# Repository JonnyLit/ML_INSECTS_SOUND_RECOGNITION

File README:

Contenuto di questa cartella:

.
├── ESP32_Code							Codice per Arduino-IDE da usare sulle ESP32.
├── 4-classes_Training_ML_Code			Codice per effettuare il training della rete neurale basata su dataset "SBCM (Smart Bee Colony Monitor)" a 4 classi.
├── RaspberryPi_Code					Replica dei path del RaspberryPi dove sono contenuti il codice del Server (python) che deve comunicare con gli esp32 ed effettuare l'inference degli audio.
├── Sensors_Network_Simulator_Code		Codici Python che simulano in modo 1:1 i codici per esp32 e per RaspberryPi (quest'ultimo è uguale a quello del Server che gira su RaspberryPi).
└── Kicad9_projects_folder				Progetto Low quiescent current board with ESP32

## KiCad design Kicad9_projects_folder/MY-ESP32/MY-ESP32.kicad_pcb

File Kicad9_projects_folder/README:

The Kicad9 project is named "MY-ESP32".

The project consists in an ESP32 board for LiFePO4 3.6V batteries or USB use,
where the quiescent currents are low in order to use the ESP32 in deep-sleep mode
without wasting too much energy. 

For example, the normal ESP32-board ('board' and not 'module') uses 
the linear regulator 'AMS1117' to convert the 5V coming from the USB 
to 3.3V used by the ESP32 module in order to work properly.
This linear regulator has a quiescent current of about 5mA (too high),
so not convenient for battery use.
The new project instead uses an efficient buck-boost (up to 96% eff) 
in order to get the 3.3V needed, with a quiescent current in the order of 40uA.
It has been also added the possibility to charge the batteries through 
the same USB port used for programming the module.
There are also some protection diodes that add up to the overall quiescent current,
when working in reverse bias (about 20-30uA total).

So, it could be supposed that a lot of current will be 
saved when working in deep sleep mode (70uA VS 5mA --> 5000/70 = 70 times less current used).

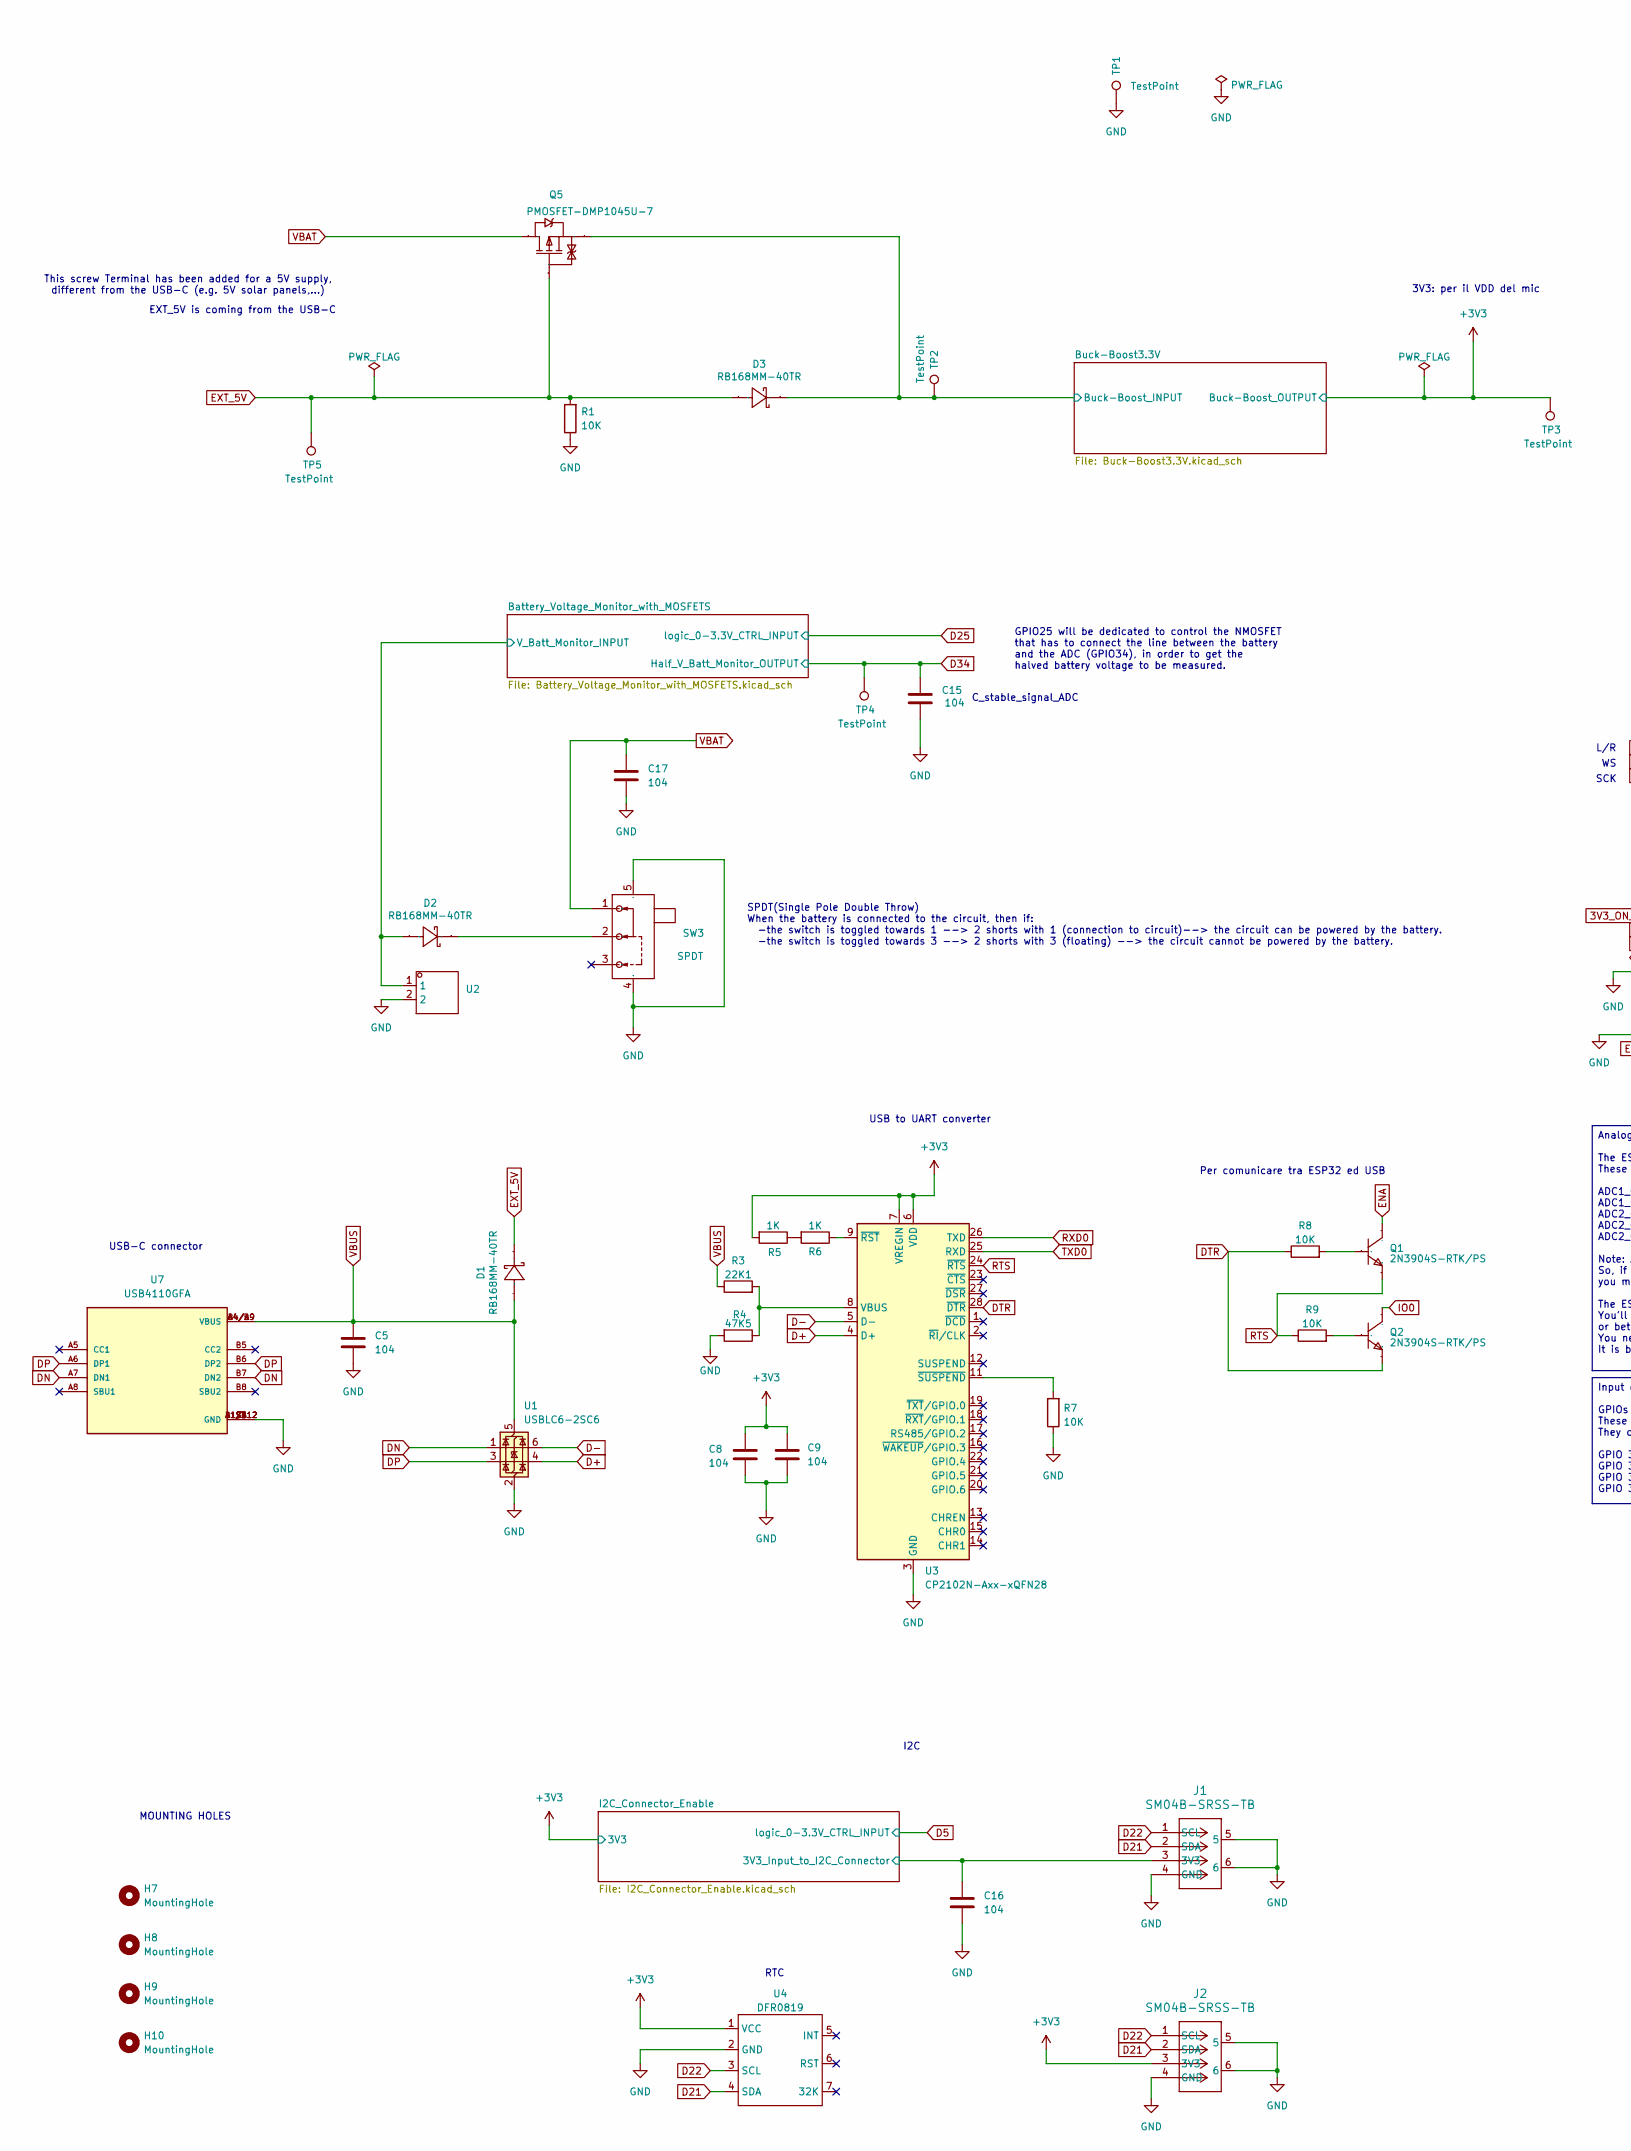
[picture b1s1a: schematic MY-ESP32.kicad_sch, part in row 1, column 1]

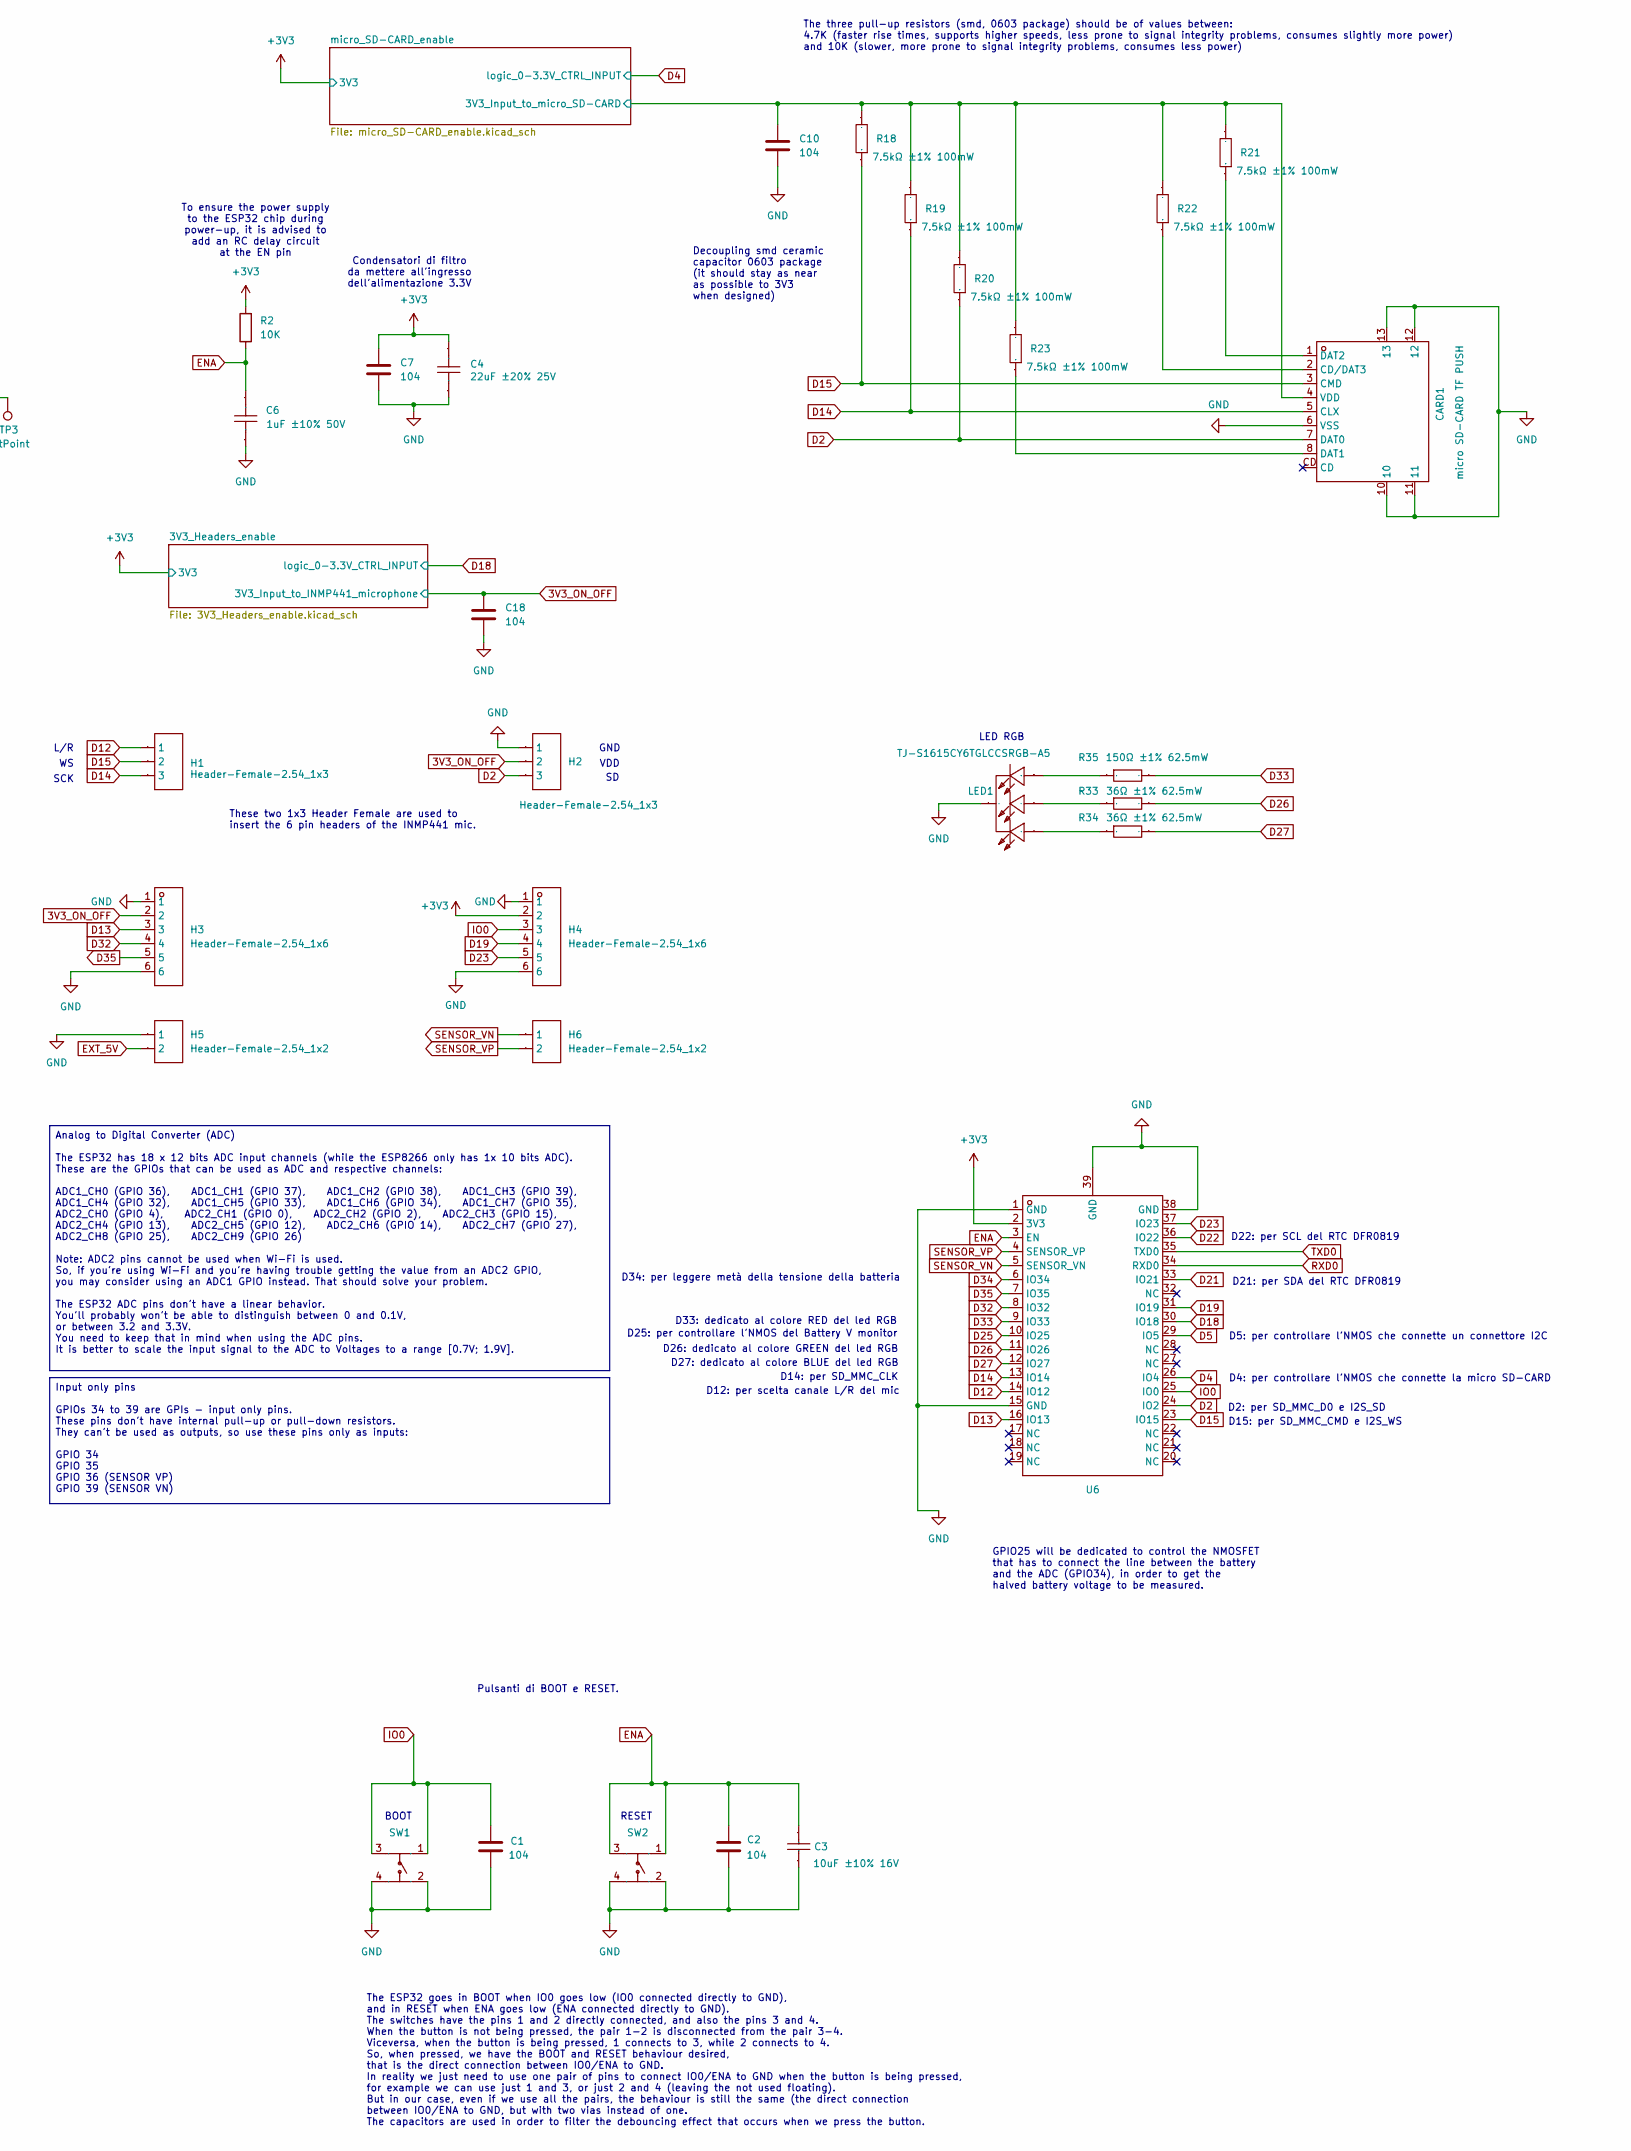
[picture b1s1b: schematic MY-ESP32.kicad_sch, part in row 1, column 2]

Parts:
C1, C2, C5, C7, C8, C9, C10, C15, C16, C17, C18: 104; C_0805_2012Metric_Pad1.18x1.45mm_HandSolder
C3: 10uF ±10% 16V; CAP_10uF_CL21A106KOQNNNE; Manufacturer Part CL21A106KOQNNNE; LCSC Part Name 10uF ±10% 16V
C4: 22uF ±20% 25V; CAP_22uF_CL21A226MAQNNNE; Manufacturer Part CL21A226MAQNNNE; LCSC Part Name 22uF ±20% 25V
C6: 1uF ±10% 50V; CL10A105KB8NNNC; Manufacturer Part CL10A105KB8NNNC; LCSC Part Name 1uF ±10% 50V
CARD1: micro SD-CARD TF PUSH; TF-SMD_TF-PUSH-micro_SD_card_slot; Manufacturer Part TF PUSH; LCSC Part Name 自弹式 MicroSD卡(TF卡) 卡座
D1, D2, D3: RB168MM-40TR; Manufacturer Part RB168MM-40TR; LCSC Part Name 电压:40V 电流:1A
H1, H2: Header-Female-2.54_1x3; Header-Female-2.54mm_1x3; Manufacturer Part 2.54-1*3P母; LCSC Part Name 间距:2.54mm 直插
H3, H4: Header-Female-2.54_1x6; Manufacturer Part 2.54-1*6P母; LCSC Part Name 间距:2.54mm 1x6P 直插
H5, H6: Header-Female-2.54_1x2; Manufacturer Part 2.54-1*2P母; LCSC Part Name 间距:2.54mm 1x2P 直插
H7, H8, H9, H10: MountingHole; MountingHole_3.2mm_M3
J1, J2: SM04B-SRSS-TB; CONN_SM04B-SRSS-TB_JST
LED1: TJ-S1615CY6TGLCCSRGB-A5; Manufacturer Part TJ-S1615CY6TGLCCSRGB-A5; LCSC Part Name RGB三色
Q1, Q2: 2N3904S-RTK/PS; 2n3904S-RTKPS; Manufacturer Part 2N3904S-RTK/PS; LCSC Part Name 2N3904S-RTK/PS
Q5: PMOSFET-DMP1045U-7; Manufacturer Part DMP1045U-7; LCSC Part Name 1个P沟道 耐压:12V 电流:4A
R1, R2, R7, R8, R9: 10K; R_0805_2012Metric_Pad1.20x1.40mm_HandSolder
R3: 22K1; R_0805_2012Metric_Pad1.20x1.40mm_HandSolder
R4: 47K5; R_0805_2012Metric_Pad1.20x1.40mm_HandSolder
R5, R6: 1K; R_0805_2012Metric_Pad1.20x1.40mm_HandSolder
R18, R19, R20, R21, R22, R23: 7.5kΩ; 0603WAF7501T5E; Manufacturer Part 0603WAF7501T5E; LCSC Part Name 7.5kΩ ±1% 100mW
R33, R34: 36Ω ±1% 62.5mW; RES_10K_0402WGF1002TCE; Manufacturer Part FRC0402J360 TS; LCSC Part Name 36Ω ±1% 62.5mW
R35: 150Ω ±1% 62.5mW; RES_10K_0402WGF1002TCE; Manufacturer Part RC0402FR-07150RL; LCSC Part Name 150Ω ±1% 62.5mW
SW1, SW2: KMR211NGLFS; Manufacturer Part KMR211NGLFS; LCSC Part Name KMR211NGLFS
SW3: SPDT; SS-12F49-G050; Manufacturer Part SS-12F49-G050; LCSC Part Name 柄长5mm 直插两档 滑动开关
TP1, TP2, TP3, TP4, TP5: TestPoint; TestPoint_Pad_D1.0mm
U1: USBLC6-2SC6; SOT-23-6
U2: CONN-TH_S2B-PH-K-S-GW; Manufacturer Part S2B-PH-K-S-GW; LCSC Part Name 1x2P 间距:2mm 弯插 系列:PH
U3: CP2102N-Axx-xQFN28; QFN-28-1EP_5x5mm_P0.5mm_EP3.35x3.35mm
U4: DFR0819
U6: WIFI-SMD_ESP32-WROVER-E-N4R8; Manufacturer Part ESP32-WROVER-E-N4R8; LCSC Part Name 通用型Wi-Fi+BT+BLE MCU模组
U7: USB4110GFA; GCT_USB4110GFA

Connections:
3V3_ON_OFF: C18.2, H2.2, H3.2; also elsewhere on the board
+3V3: C4.2, C7.1, C8.1, C9.1, H4.2, J2.3 (3V3), R2.2, R5.2, TP3.1, U3.6 (VDD), U3.7 (VREGIN), U4.1 (VCC), U6.2 (3V3); also elsewhere on the board
/Battery_Voltage_Monitor_with_MOSFETS/V_Batt_Monitor_INPUT: D2.2 (A), U2.1; also elsewhere on the board
/Buck-Boost3.3V/Buck-Boost_INPUT: D3.1 (C), Q5.2 (S), TP2.1; also elsewhere on the board
/I2C_Connector_Enable/3V3_Input_to_I2C_Connector: C16.2, J1.3 (3V3); also elsewhere on the board
/micro_SD-CARD_enable/3V3_Input_to_micro_SD-CARD: C10.2, CARD1.4 (VDD), R18.2, R19.2, R20.2, R21.2, R22.2, R23.2; also elsewhere on the board
D2: CARD1.7 (DAT0), H2.3, R20.1, U6.24 (IO2)
D4: U6.26 (IO4); also elsewhere on the board
D5: U6.29 (IO5); also elsewhere on the board
D12: H1.1, U6.14 (IO12)
D13: H3.3, U6.16 (IO13)
D14: CARD1.5 (CLX), H1.3, R19.1, U6.13 (IO14)
D15: CARD1.3 (CMD), H1.2, R18.1, U6.23 (IO15)
D18: U6.30 (IO18); also elsewhere on the board
D19: H4.4, U6.31 (IO19)
D21: J1.2 (SDA), J2.2 (SDA), U4.4 (SDA), U6.33 (IO21)
D22: J1.1 (SCL), J2.1 (SCL), U4.3 (SCL), U6.36 (IO22)
D23: H4.5, U6.37 (IO23)
D25: U6.10 (IO25); also elsewhere on the board
D26: R33.2, U6.11 (IO26)
D27: R34.2, U6.12 (IO27)
D32: H3.4, U6.8 (IO32)
D33: R35.2, U6.9 (IO33)
D34: C15.1, TP4.1, U6.6 (IO34); also elsewhere on the board
D35: H3.5, U6.7 (IO35)
D+: U1.4 (I/O2), U3.4 (D+)
D-: U1.6 (I/O1), U3.5 (D-)
DN: U1.1 (I/O1), U7.A7 (DN1), U7.B7 (DN2)
DP: U1.3 (I/O2), U7.A6 (DP1), U7.B6 (DP2)
DTR: Q2.1 (E), R8.1, U3.28 (~DTR)
ENA: C2.1, C3.2, C6.2, Q1.3 (C), R2.1, SW2.1, SW2.3, U6.3 (EN)
EXT_5V: D1.1 (C), D3.2 (A), H5.2, Q5.1 (G), R1.2, TP5.1
GND: C1.2, C2.2, C3.1, C4.1, C5.2, C6.1, C7.2, C8.2, C9.2, C10.1, C15.2, C16.1, C17.1, C18.1, CARD1.6 (VSS), CARD1.10, CARD1.11, CARD1.12, CARD1.13, H2.1, H3.1, H3.6, H4.1, H4.6, H5.1, J1.4 (GND), J1.5, J1.6, J2.4 (GND), J2.5, J2.6, LED1.1 (C), R1.1, R4.2, R7.1, SW1.2, SW1.4, SW2.2, SW2.4, SW3.4, SW3.5, TP1.1, U1.2 (GND), U2.2, U3.3 (GND), U3.29 (GND), U4.2 (GND), U6.1 (GND), U6.15 (GND), U6.38 (GND), U6.39 (GND), U7.A1/B12 (GND), U7.B1/A12 (GND), U7.S1 (GND), U7.S2 (GND), U7.S3 (GND), U7.S4 (GND); also elsewhere on the board
IO0: C1.1, H4.3, Q2.3 (C), SW1.1, SW1.3, U6.25 (IO0)
unnamed: CARD1.2 (CD/DAT3), R22.1
unnamed: CARD1.8 (DAT1), R23.1
unnamed: CARD1.1 (DAT2), R21.1
unnamed: D2.1 (C), SW3.2
unnamed: LED1.2 (B), R34.1
unnamed: LED1.3 (G), R33.1
unnamed: LED1.4 (R), R35.1
unnamed: Q1.2 (B), R8.2
unnamed: Q2.2 (B), R9.2
unnamed: R5.1, R6.2
unnamed: R3.2, R4.1, U3.8 (VBUS)
unnamed: R6.1, U3.9 (~RST)
unnamed: R7.2, U3.11 (~SUSPEND)
RTS: Q1.1 (E), R9.1, U3.24 (~RTS)
RXD0: U3.26 (TXD), U6.34 (RXD0)
SENSOR_VN: H6.1, U6.5 (SENSOR_VN)
SENSOR_VP: H6.2, U6.4 (SENSOR_VP)
TXD0: U3.25 (RXD), U6.35 (TXD0)
VBAT: C17.2, Q5.3 (D), SW3.1
VBUS: C5.1, D1.2 (A), R3.1, U1.5 (VBUS), U7.A4/B9 (VBUS), U7.B4/A9 (VBUS)

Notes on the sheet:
VDD
D14: per SD_MMC_CLK
3V3: per il VDD del mic
GPIO25 will be dedicated to control the NMOSFET that has to connect the line between the battery and the ADC (GPIO34), in order to get the halved battery voltage to be measured.
This screw Terminal has been added for a 5V supply, different from the USB-C (e.g. 5V solar panels,...)
RTC
D33: dedicato al colore RED del led RGB
L/R
GND
D2: per SD_MMC_D0 e I2S_SD
SCK
MOUNTING HOLES
Decoupling smd ceramic capacitor 0603 package (it should stay as near as possible to 3V3 when designed)
Per comunicare tra ESP32 ed USB
D26: dedicato al colore GREEN del led RGB
Pulsanti di BOOT e RESET.
The three pull-up resistors (smd, 0603 package) should be of values between: 4.7K (faster rise times, supports higher speeds, less prone to signal integrity problems, consumes slightly more power) and 10K (slower, more prone to signal integrity problems, consumes less power)
The ESP32 goes in BOOT when IO0 goes low (IO0 connected directly to GND), and in RESET when ENA goes low (ENA connected directly to GND). The switches have the pins 1 and 2 directly connected, and also the pins 3 and 4. When the button is not being pressed, the pair 1-2 is disconnected from the pai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
D22: per SCL del RTC DFR0819
LED RGB
Condensatori di filtro da mettere all'ingresso dell'alimentazione 3.3V
EXT_5V is coming from the USB-C
D5: per controllare l'NMOS che connette un connettore I2C
D12: per scelta canale L/R del mic
USB to UART converter
RESET
D25: per controllare l'NMOS del Battery V monitor
D27: dedicato al colore BLUE del led RGB
To ensure the power supply to the ESP32 chip during power-up, it is advised to add an RC delay circuit at the EN pin
D15: per SD_MMC_CMD e I2S_WS
SPDT(Single Pole Double Throw) When the battery is connected to the circuit, then if: -the switch is toggled towards 1 --> 2 shorts with 1 (connection to circuit)--> the circuit can be powered by the battery. -the switch is toggled towards 3 --> 2 shorts with 3 (floating) --> the circuit cannot be 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
I2C
USB-C connector
D21: per SDA del RTC DFR0819
These two 1x3 Header Female are used to insert the 6 pin headers of the INMP441 mic.
C_stable_signal_ADC
BOOT
D34: per leggere metà della tensione della batteria
D4: per controllare l'NMOS che connette la micro SD-CARD
Input only pins GPIOs 34 to 39 are GPIs - input only pins. These pins don't have internal pull-up or pull-down resistors. They can't be used as outputs, so use these pins only as inputs: GPIO 34 GPIO 35 GPIO 36 (SENSOR VP) GPIO 39 (SENSOR VN)

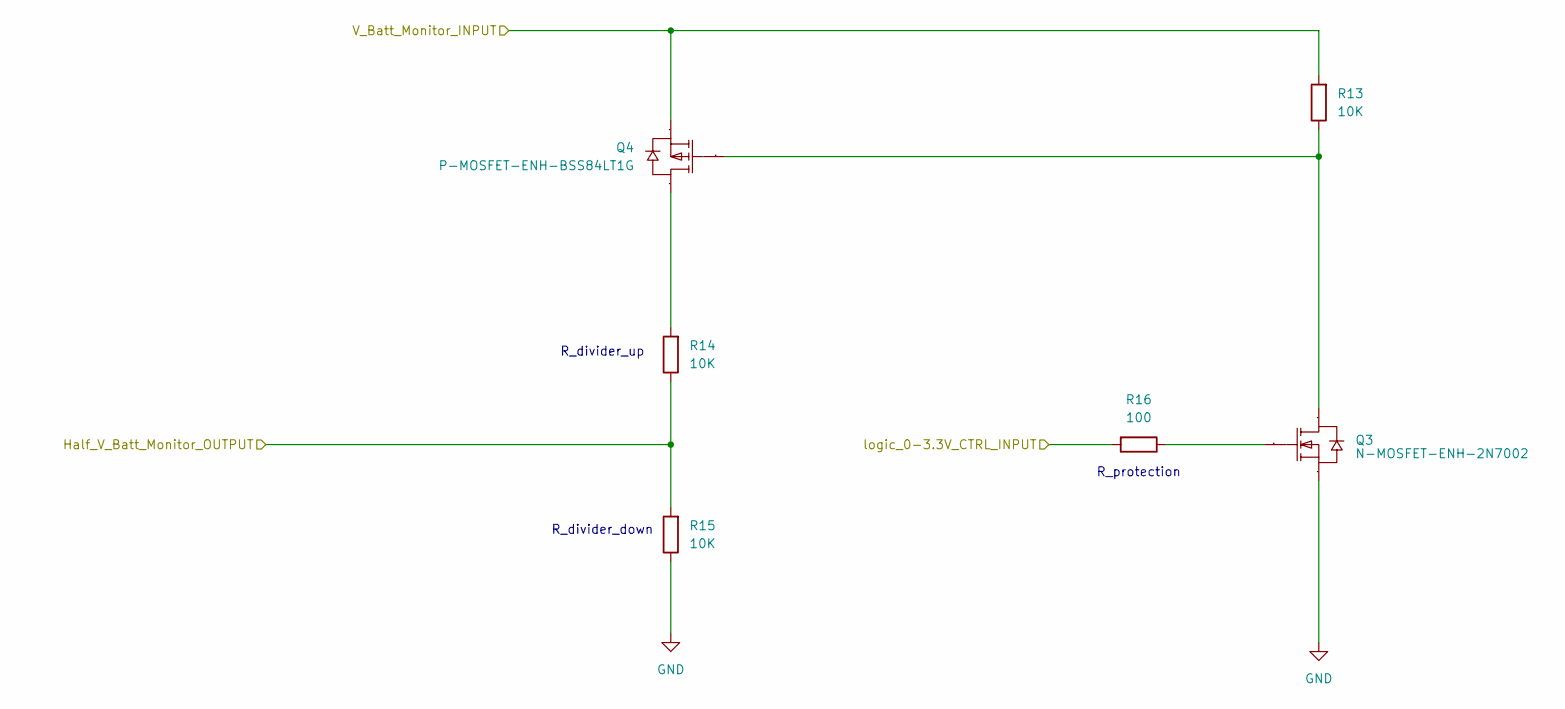
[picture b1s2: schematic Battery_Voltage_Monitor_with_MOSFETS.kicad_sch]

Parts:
Q3: N-MOSFET-ENH-2N7002; 2N7002; Manufacturer Part 2N7002; LCSC Part Name 1个N沟道 耐压:60V 电流:115mA
Q4: P-MOSFET-ENH-BSS84LT1G; BSS84LT1G; Manufacturer Part BSS84LT1G; LCSC Part Name 1个P沟道 耐压:50V 电流:130mA
R13, R14, R15: 10K; R_0805_2012Metric_Pad1.20x1.40mm_HandSolder
R16: 100; R_0805_2012Metric_Pad1.20x1.40mm_HandSolder

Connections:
/Battery_Voltage_Monitor_with_MOSFETS/V_Batt_Monitor_INPUT: Q4.2 (S), R13.2; also elsewhere on the board
D25: R16.2; also elsewhere on the board
D34: R14.1, R15.2; also elsewhere on the board
GND: Q3.2 (S), R15.1; also elsewhere on the board
unnamed: Q3.3 (D), Q4.1 (G), R13.1
unnamed: Q3.1 (G), R16.1
unnamed: Q4.3 (D), R14.2

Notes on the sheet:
R_divider_down
R_divider_up
R_protection

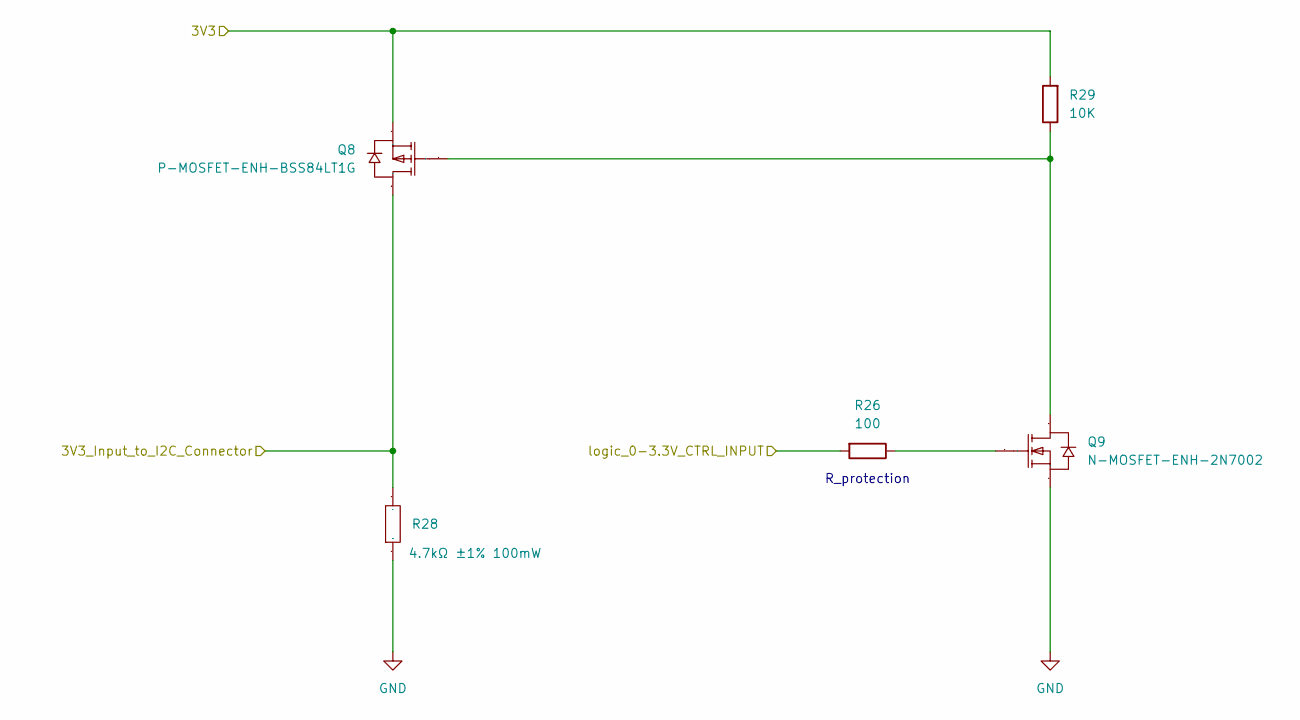
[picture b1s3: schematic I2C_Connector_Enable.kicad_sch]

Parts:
Q8: P-MOSFET-ENH-BSS84LT1G; BSS84LT1G; Manufacturer Part BSS84LT1G; LCSC Part Name 1个P沟道 耐压:50V 电流:130mA
Q9: N-MOSFET-ENH-2N7002; 2N7002; Manufacturer Part 2N7002; LCSC Part Name 1个N沟道 耐压:60V 电流:115mA
R26: 100; R_0805_2012Metric_Pad1.20x1.40mm_HandSolder
R28: 4.7kΩ ±1% 100mW; 0603WAF4701T5E; Manufacturer Part 0603WAF4701T5E; LCSC Part Name 4.7kΩ ±1% 100mW
R29: 10K; R_0805_2012Metric_Pad1.20x1.40mm_HandSolder

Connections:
+3V3: Q8.2 (S), R29.2; also elsewhere on the board
/I2C_Connector_Enable/3V3_Input_to_I2C_Connector: Q8.3 (D), R28.2; also elsewhere on the board
D5: R26.2; also elsewhere on the board
GND: Q9.2 (S), R28.1; also elsewhere on the board
unnamed: Q8.1 (G), Q9.3 (D), R29.1
unnamed: Q9.1 (G), R26.1

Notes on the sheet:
R_protection

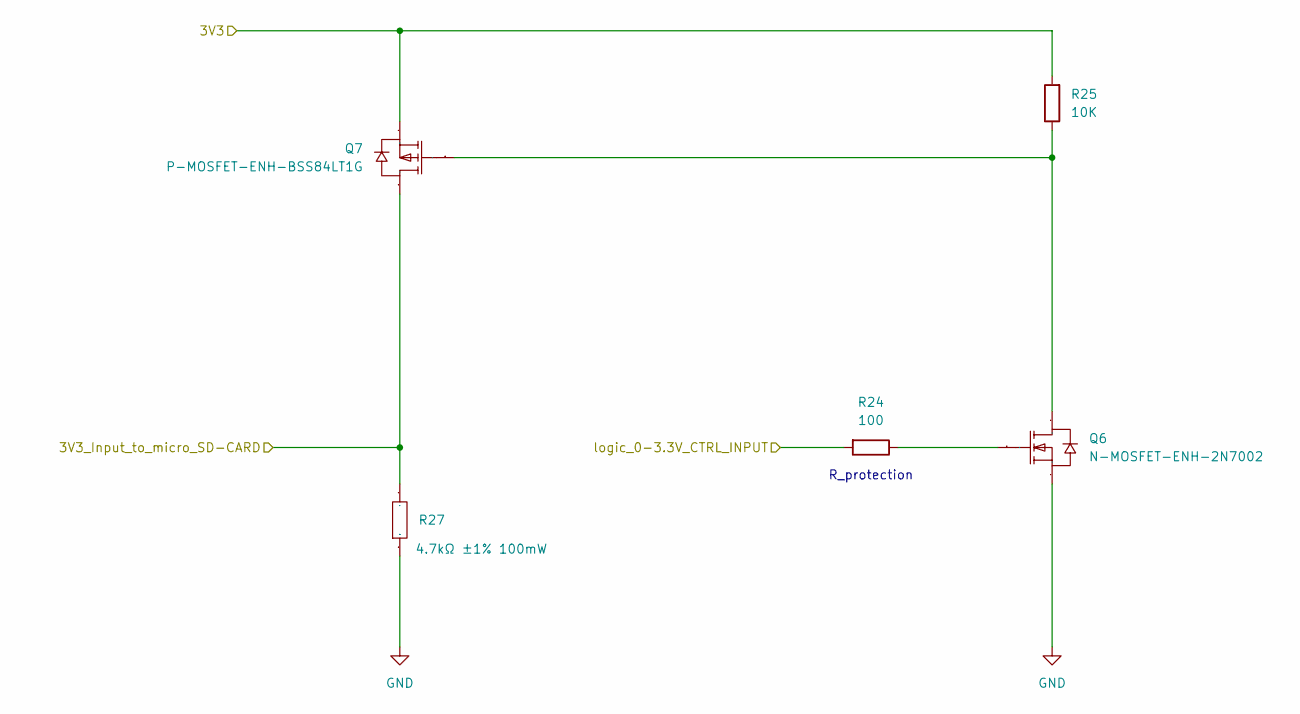
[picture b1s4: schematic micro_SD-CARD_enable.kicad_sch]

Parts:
Q6: N-MOSFET-ENH-2N7002; 2N7002; Manufacturer Part 2N7002; LCSC Part Name 1个N沟道 耐压:60V 电流:115mA
Q7: P-MOSFET-ENH-BSS84LT1G; BSS84LT1G; Manufacturer Part BSS84LT1G; LCSC Part Name 1个P沟道 耐压:50V 电流:130mA
R24: 100; R_0805_2012Metric_Pad1.20x1.40mm_HandSolder
R25: 10K; R_0805_2012Metric_Pad1.20x1.40mm_HandSolder
R27: 4.7kΩ ±1% 100mW; 0603WAF4701T5E; Manufacturer Part 0603WAF4701T5E; LCSC Part Name 4.7kΩ ±1% 100mW

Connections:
+3V3: Q7.2 (S), R25.2; also elsewhere on the board
/micro_SD-CARD_enable/3V3_Input_to_micro_SD-CARD: Q7.3 (D), R27.2; also elsewhere on the board
D4: R24.2; also elsewhere on the board
GND: Q6.2 (S), R27.1; also elsewhere on the board
unnamed: Q6.3 (D), Q7.1 (G), R25.1
unnamed: Q6.1 (G), R24.1

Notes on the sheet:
R_protection

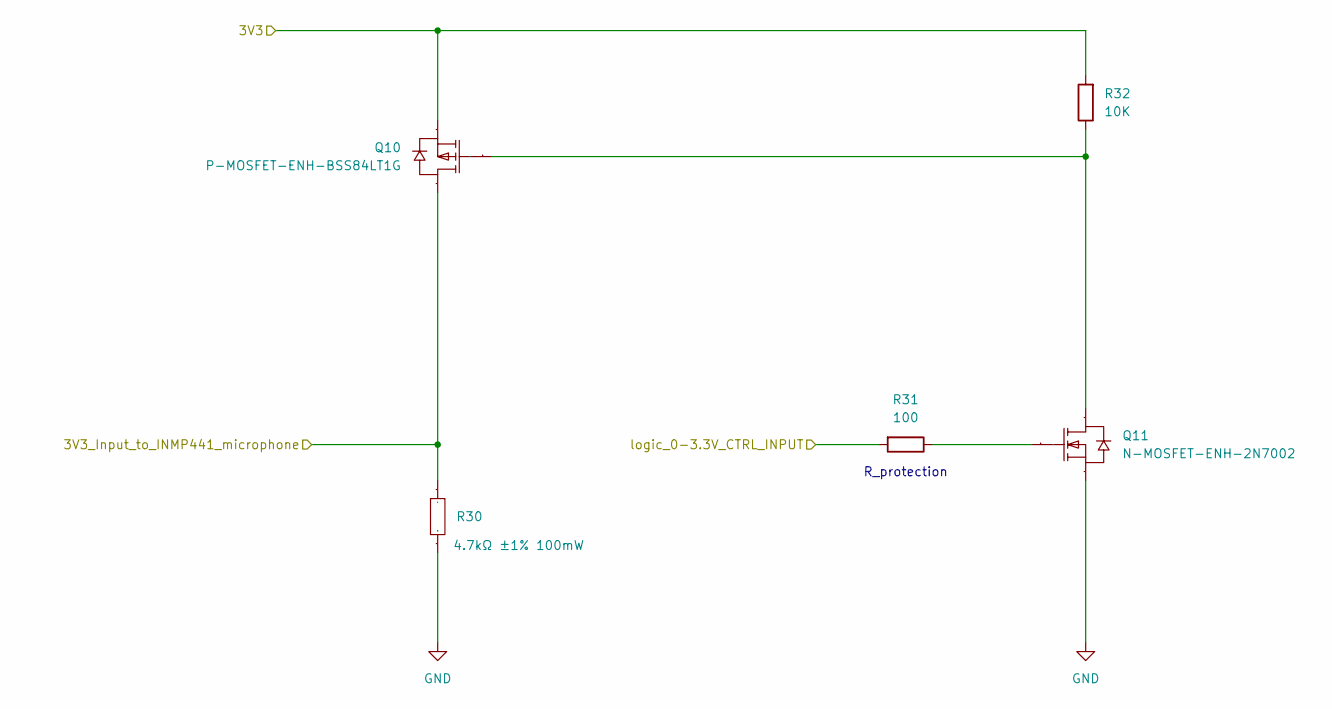
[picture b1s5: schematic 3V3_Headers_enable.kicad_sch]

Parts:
Q10: P-MOSFET-ENH-BSS84LT1G; BSS84LT1G; Manufacturer Part BSS84LT1G; LCSC Part Name 1个P沟道 耐压:50V 电流:130mA
Q11: N-MOSFET-ENH-2N7002; 2N7002; Manufacturer Part 2N7002; LCSC Part Name 1个N沟道 耐压:60V 电流:115mA
R30: 4.7kΩ ±1% 100mW; 0603WAF4701T5E; Manufacturer Part 0603WAF4701T5E; LCSC Part Name 4.7kΩ ±1% 100mW
R31: 100; R_0805_2012Metric_Pad1.20x1.40mm_HandSolder
R32: 10K; R_0805_2012Metric_Pad1.20x1.40mm_HandSolder

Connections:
3V3_ON_OFF: Q10.3 (D), R30.2; also elsewhere on the board
+3V3: Q10.2 (S), R32.2; also elsewhere on the board
D18: R31.2; also elsewhere on the board
GND: Q11.2 (S), R30.1; also elsewhere on the board
unnamed: Q10.1 (G), Q11.3 (D), R32.1
unnamed: Q11.1 (G), R31.1

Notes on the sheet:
R_protection

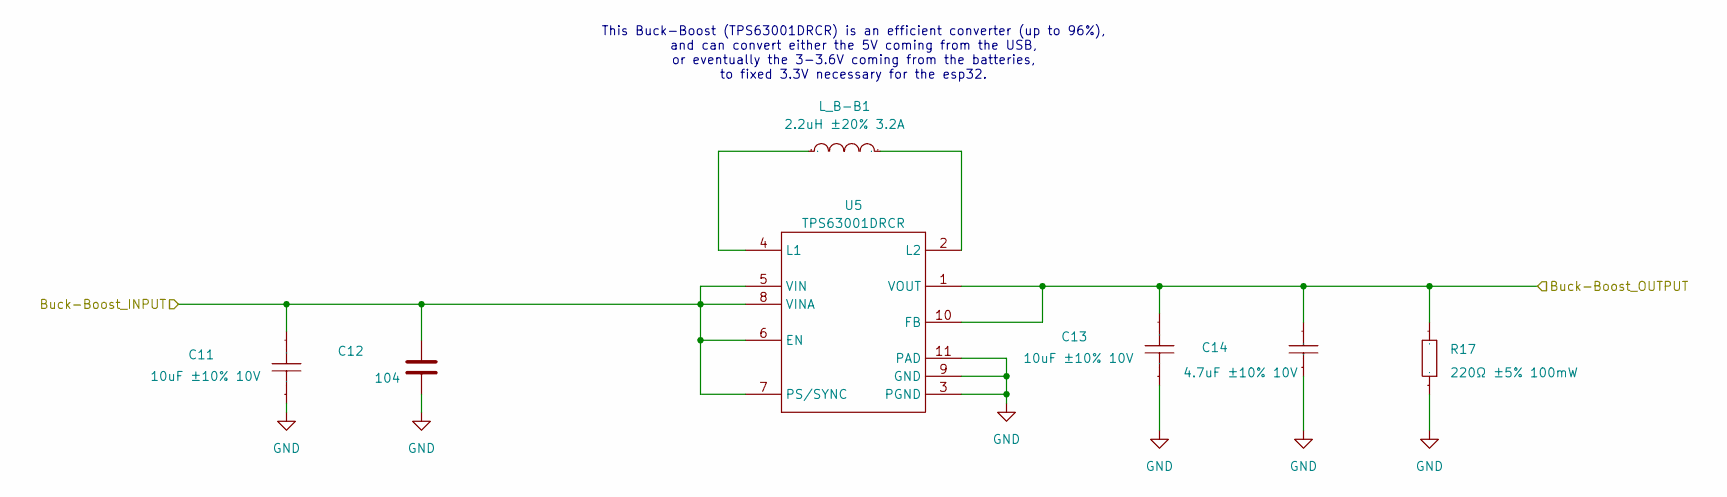
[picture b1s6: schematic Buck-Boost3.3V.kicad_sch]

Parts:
C11, C13: 10uF ±10% 10V; CL10A106KP8NNNC; Manufacturer Part CL10A106KP8NNNC; LCSC Part Name 10uF ±10% 10V
C12: 104; C_0805_2012Metric_Pad1.18x1.45mm_HandSolder
C14: 4.7uF; CL10A475KP8NNNC; Manufacturer Part CL10A475KP8NNNC; LCSC Part Name 4.7uF ±10% 10V
L_B-B1: 2.2uH ±20% 3.2A; IND_2.2uH_SWPA4018S2R2MT; Manufacturer Part SWPA4018S2R2MT; LCSC Part Name 2.2uH ±20% 3.2A
R17: 220Ω; 0603WAJ0221T5E; Manufacturer Part 0603WAJ0221T5E; LCSC Part Name 220Ω ±5% 100mW
U5: TPS63001DRCR; Manufacturer Part TPS63001DRCR; LCSC Part Name 高效率单电感升降压转换器

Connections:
+3V3: C13.2, C14.2, R17.2, U5.1 (VOUT), U5.10 (FB); also elsewhere on the board
/Buck-Boost3.3V/Buck-Boost_INPUT: C11.2, C12.1, U5.5 (VIN), U5.6 (EN), U5.7 (PS/SYNC), U5.8 (VINA); also elsewhere on the board
GND: C11.1, C12.2, C13.1, C14.1, R17.1, U5.3 (PGND), U5.9 (GND), U5.11 (PAD); also elsewhere on the board
unnamed: L_B-B1.1, U5.4 (L1)
unnamed: L_B-B1.2, U5.2 (L2)

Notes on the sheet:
This Buck-Boost (TPS63001DRCR) is an efficient converter (up to 96%), and can convert either the 5V coming from the USB, or eventually the 3-3.6V coming from the batteries, to fixed 3.3V necessary for the esp32.

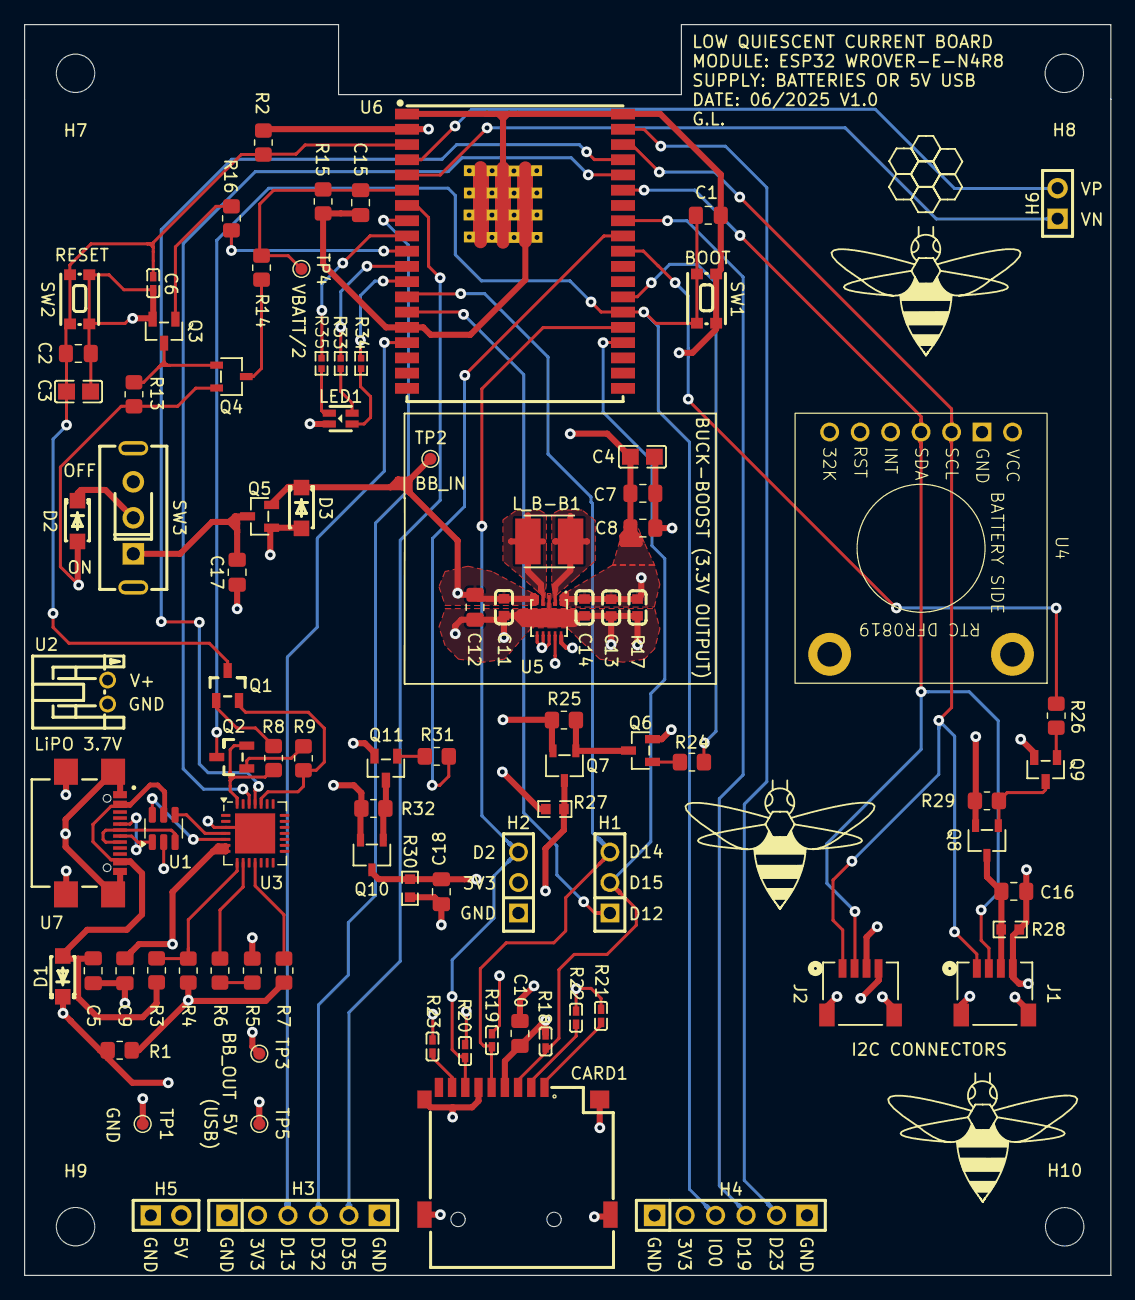
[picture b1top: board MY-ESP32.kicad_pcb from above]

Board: 4 copper layers, 90.5 x 104.2 mm, 94 parts (0 on the bottom side), 65 nets.

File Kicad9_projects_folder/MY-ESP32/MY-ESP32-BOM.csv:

Designator,Comment,Footprint,JLCPCB Part #
"C1, C2, C5, C7, C8, C9, C10, C12, C15, C16, C17, C18",104,Capacitor_SMD:C_0805_2012Metric_Pad1.18x1.45mm_HandSolder,C49678
C3,10uF ±10% 16V,My_Personal_Footprints_Library:CAP_10uF_CL21A106KOQNNNE,C1713
C4,22uF ±20% 25V,My_Personal_Footprints_Library:CAP_22uF_CL21A226MAQNNNE,C45783
C6,1uF ±10% 50V,My_Personal_Footprints_Library:CL10A105KB8NNNC,C15849
"C11, C13",10uF ±10% 10V,My_Personal_Footprints_Library:CL10A106KP8NNNC,C19702
C14,4.7uF,My_Personal_Footprints_Library:CL10A475KP8NNNC,C1705
CARD1,micro SD-CARD TF PUSH,My_Personal_Footprints_Library:TF-SMD_TF-PUSH-micro_SD_card_slot,C393941
"D1, D2, D3",RB168MM-40TR,My_Personal_Footprints_Library:RB168MM-40TR,C509936
"H1, H2",Header-Female-2.54_1x3,My_Personal_Footprints_Library:Header-Female-2.54mm_1x3,C146243
"H5, H6",Header-Female-2.54_1x6,My_Personal_Footprints_Library:Header-Female-2.54_1x6,C40877
H7,Header-Female-2.54_1x2,My_Personal_Footprints_Library:Header-Female-2.54_1x2,C49661
H8,Header-Female-2.54_1x2,My_Personal_Footprints_Library:Header-Female-2.54_1x2,C49661
"J1, J2",SM04B-SRSS-TB,My_Personal_Footprints_Library:CONN_SM04B-SRSS-TB_JST,
L_B-B1,2.2uH ±20% 3.2A,My_Personal_Footprints_Library:IND_2.2uH_SWPA4018S2R2MT,C50543
LED1,E6C0606RGBC3UDA,My_Personal_Footprints_Library:E6C0606RGBC3UDA,C375569
"Q1, Q2",2N3904S-RTK/PS,My_Personal_Footprints_Library:2n3904S-RTKPS,C18536
"Q3, Q7, Q10, Q12",N-MOSFET-ENH-2N7002,My_Personal_Footprints_Library:2N7002,C8545
"Q4, Q8, Q9, Q11",P-MOSFET-ENH-BSS84LT1G,My_Personal_Footprints_Library:BSS84LT1G,C82079
Q5,PMOSFET-DMP1045U-7,My_Personal_Footprints_Library:PMOSFET-DMP1045U-7,C177033
"R1, R2, R7, R8, R9, R13, R14, R15, R25, R29, R32",10K,Resistor_SMD:R_0805_2012Metric_Pad1.20x1.40mm_HandSolder,C17414
R3,22K1,Resistor_SMD:R_0805_2012Metric_Pad1.20x1.40mm_HandSolder,C2930182
R4,47K5,Resistor_SMD:R_0805_2012Metric_Pad1.20x1.40mm_HandSolder,C245335
"R5, R6",1K,Resistor_SMD:R_0805_2012Metric_Pad1.20x1.40mm_HandSolder,C17513
R10,150Ω ±1% 62.5mW,My_Personal_Footprints_Library:RES_10K_0402WGF1002TCE,C138054
"R11, R12",36Ω ±1% 62.5mW,My_Personal_Footprints_Library:RES_10K_0402WGF1002TCE,C2906935
"R16, R24, R26, R31",100,Resistor_SMD:R_0805_2012Metric_Pad1.20x1.40mm_HandSolder,C17408
R17,220Ω,My_Personal_Footprints_Library:0603WAJ0221T5E,C1226
"R18, R19, R20, R21, R22, R23",7.5kΩ,My_Personal_Footprints_Library:0603WAF7501T5E,C23234
"R27, R28, R30",4.7kΩ ±1% 100mW,My_Personal_Footprints_Library:0603WAF4701T5E,C23162
"SW1, SW2",KMR211NGLFS,My_Personal_Footprints_Library:KMR211NGLFS,C221676
SW3,SPDT,My_Personal_Footprints_Library:SS-12F49-G050,C2876010
"TP1, TP2, TP3, TP4, TP5",TestPoint,TestPoint:TestPoint_Pad_D1.0mm,
U1,USBLC6-2SC6,Package_TO_SOT_SMD:SOT-23-6,C2827654
U2,CONN-TH_S2B-PH-K-S-GW,My_Personal_Footprints_Library:CONN-TH_S2B-PH-K-S-GW,C157932
U3,CP2102N-Axx-xQFN28,Package_DFN_QFN:QFN-28-1EP_5x5mm_P0.5mm_EP3.35x3.35mm,C964632
U4,DFR0819,My_Personal_Footprints_Library:DFR0819,
U5,TPS63001DRCR,My_Personal_Footprints_Library:TPS63001DRCR,C28060
U6,ESP32-WROVER-E-N4R8,My_Personal_Footprints_Library:WIFI-SMD_ESP32-WROVER-E-N4R8,C967023
U7,USB4110GFA,My_Personal_Footprints_Library:GCT_USB4110GFA,

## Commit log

2024-11-17 First commit
    upload of the folders without datasets: Red_Palm_Weevil, Rock_Paper_Scissors
2024-11-19 Second commit
    update of the folders + Overview.pdf
2024-11-19 Third commit
    adding 'Schermata Raspberry-Pi.png'
2024-11-20 Fourth commit
    Diario.txt'
2024-11-20 Fifth commit
2024-12-19 third commit
    aggiunta file di inference per spettrogrammi RPW, file python per simulazione rete MQTT, e pdf per illustrare il funzionamento della rete MQTT
2025-01-10 1st commit
2025-01-10 deleted everything
2025-01-10 reload everything
2025-01-10 1st commit
    update of Red_Palm_Weevil/AudioPreprocessing_Server_new.py
2025-01-10 2nd commit
2025-06-06 Second commit
2025-06-09 Third commit
2025-06-13 Fourth commit
2025-06-16 5th commit
2025-06-18 6th commit
2025-07-10 7th commit
2025-07-11 8th commit
2025-07-26 9th commit
2025-11-05 10th commit
